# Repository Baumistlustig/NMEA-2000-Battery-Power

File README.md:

# NMEA 2000 Battery Power

This is a project, which reads the voltage and current of a battery, and posts it to a NMEA 2000 BUS.

The project uses an ESP32 & the SN65HVD230 for CAN BUS communication. If the voltage falls under a certain value, a contactor will automatically disconnect the battery from the rest of the circuit to prevent drain. 

Additionally, it posts the voltage, current and temperature into the N2k bus where it can be worked with by other devices.

## Table of Contents

- [Electrical](/Electrical) A KiCad project 
- [Software](/Software) A PlatformIO project

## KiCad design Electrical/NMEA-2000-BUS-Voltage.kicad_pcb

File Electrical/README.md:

# Electrical

  The KiCad project

  ## Table of Contents

  - [Symbol](/Electrical/Symbol) The Symbols for the schematics
  - [Datasheets](/Electrical/Datasheets) Datasheets of the components
  - [3D-Models](/Electrical/3D-Models) 3D-Models for the PCB
  - [Footprints](/Electrical/Footprints) Footprins for the PCB

## Components-List

A list of all the electrical components I used for the project:

- [ESP32 WROOM-32E](/Electrical/Datasheets/esp32-wroom-32e.pdf) Microcontroller
- [SN65HVD230](/Electrical/Datasheets/sn76hvd230.pdf) CAN Transceiver
- [BME280](/Electrical/Datasheets/bme280.pdf) Environment temp- & humidity sensor
- [ADS131M08](/Electrical/Datasheets/ads131m08-q1.pdf) 24-bit, 8 channel ADC
- [HO 150-S-SP30.pdf](/Electrical/Datasheets/HO-150-S-SP30.pdf) 150A current transducer
- [IRFZ44N](/Electrical/Datasheets/IRFZ44N.pdf) N-Channel MOSFET
- [LM7850](/Electrical/Datasheets/MC7800-D.PDF) 12-5V voltage regulator
- [AMS1117](/Electrical/Datasheets/ams1117.pdf) 5-3.3V voltage regulator
- [B57703M](/Electrical/Datasheets/B57703M-Thermistor.pdf) 10k NTC Thermistor
- ([ADR4533](/Electrical/Datasheets/ADR4533.pdf) 3.3V reference voltage source)

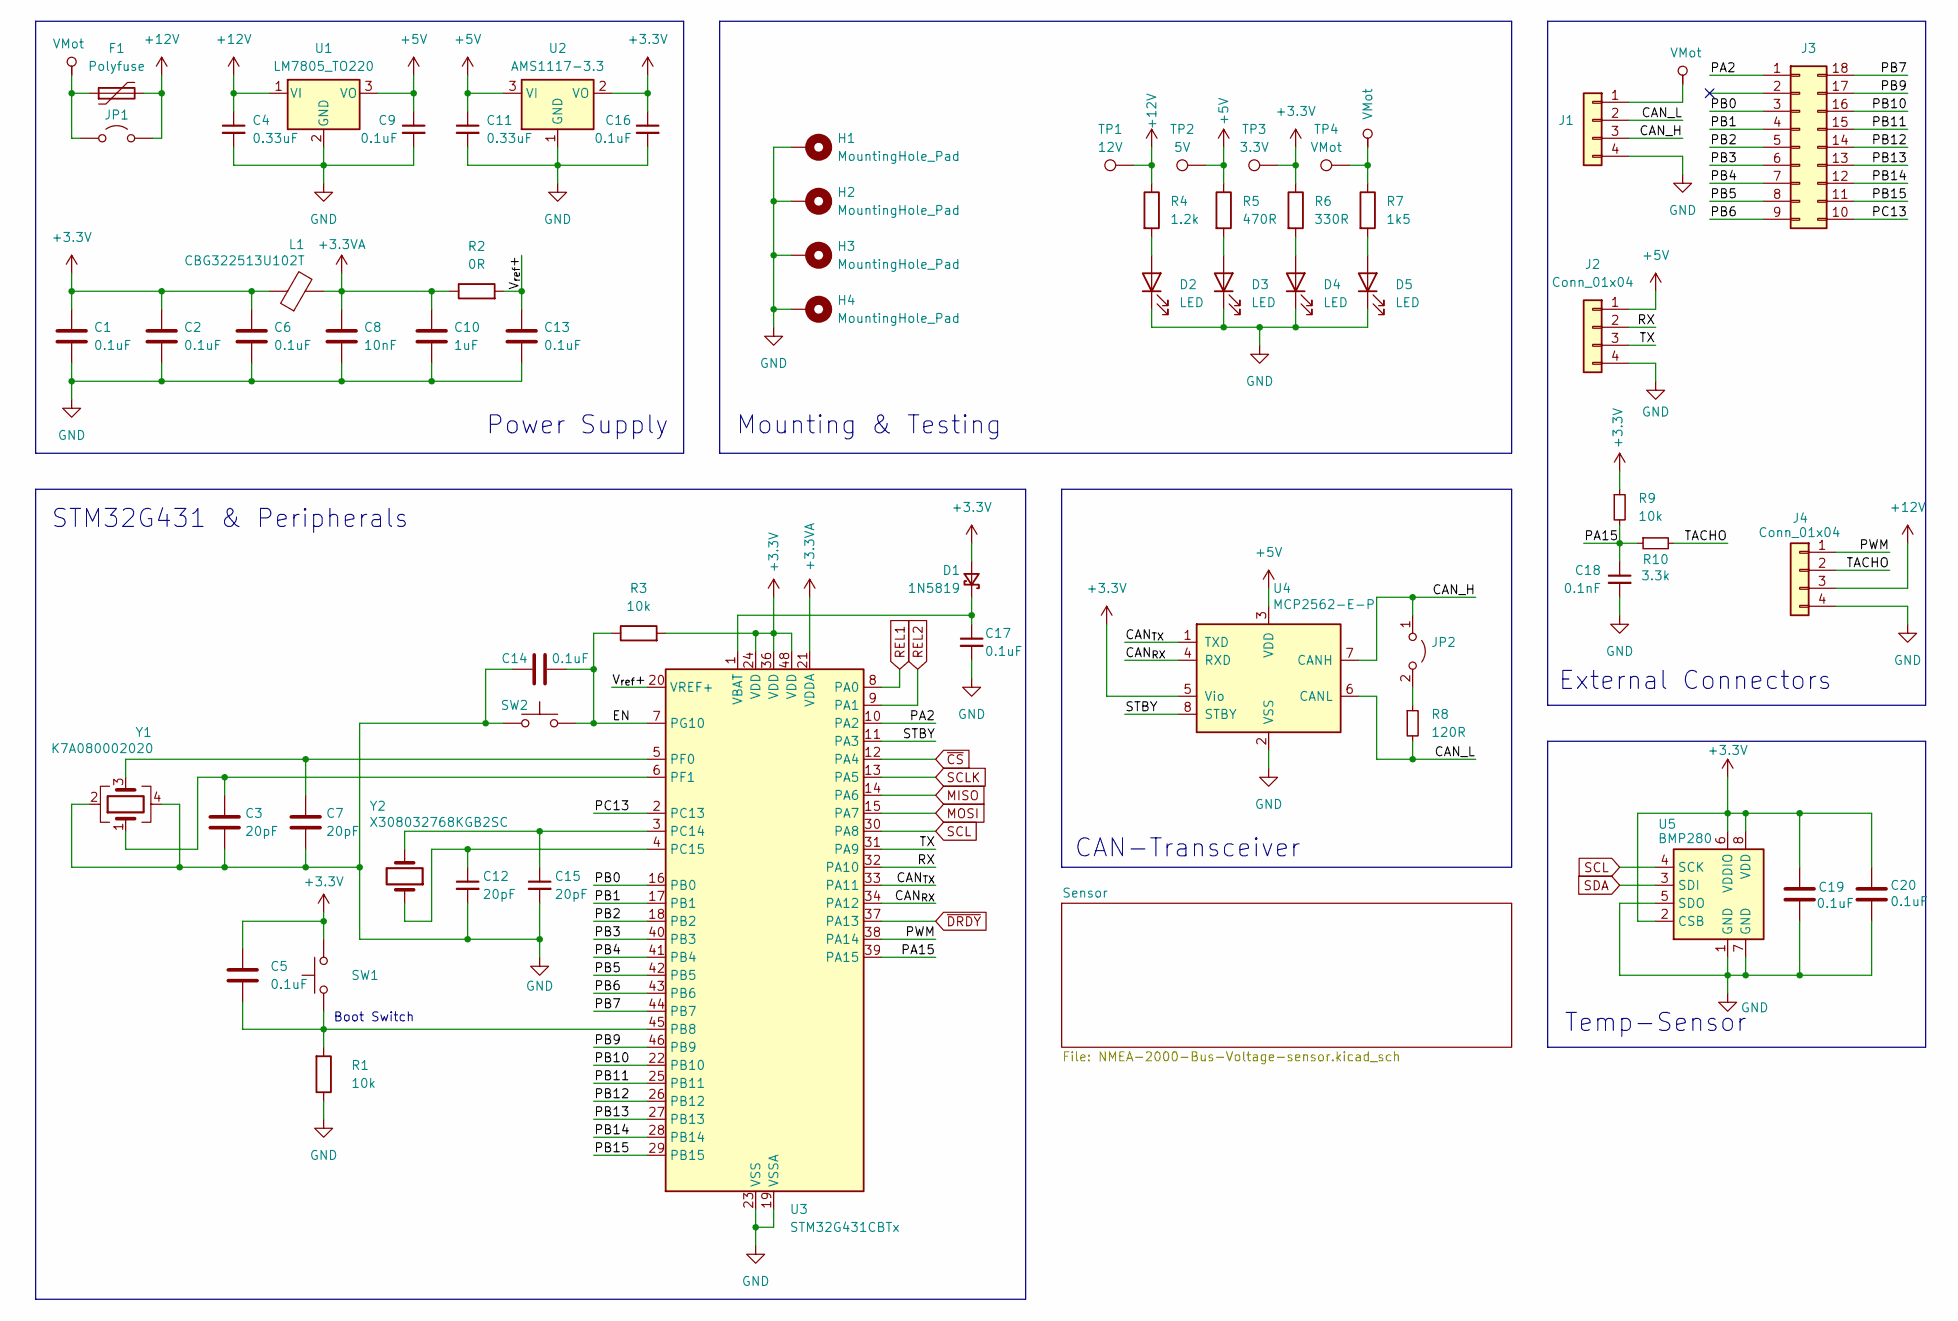
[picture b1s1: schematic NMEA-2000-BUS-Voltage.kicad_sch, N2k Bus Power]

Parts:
C1, C2, C5, C6, C9, C13, C14, C16, C17, C19, C20: 0.1uF; C_Disc_D5.0mm_W2.5mm_P5.00mm
C3, C7, C12, C15: 20pF; C_Disc_D5.0mm_W2.5mm_P5.00mm
C4, C11: 0.33uF; C_Disc_D5.0mm_W2.5mm_P5.00mm
C8: 10nF; C_Disc_D5.0mm_W2.5mm_P5.00mm
C10: 1uF; C_Disc_D5.0mm_W2.5mm_P5.00mm
C18: 0.1nF; C_Disc_D5.0mm_W2.5mm_P5.00mm
D1: 1N5819; D_DO-41_SOD81_P10.16mm_Horizontal
D2, D3, D4, D5: LED; LED_D5.0mm
F1: Polyfuse; D_1210_3225Metric_Pad1.42x2.65mm_HandSolder
H1, H2, H3, H4: MountingHole_Pad; MountingHole_6mm_Pad
J1: Conn_01x04; TerminalBlock_Phoenix_PT-1,5-4-5.0-H_1x04_P5.00mm_Horizontal
J2: Conn_01x04; PinSocket_1x04_P2.54mm_Horizontal
J3: Conn_02x08_Counter_Clockwise; PinHeader_2x09_P2.54mm_Vertical
J4: Conn_01x04; FanPinHeader_1x04_P2.54mm_Vertical
JP1, JP2: Jumper_2_Open; PinHeader_1x02_P2.54mm_Vertical
L1: CBG322513U102T; L_1210_3225Metric_Pad1.42x2.65mm_HandSolder
R1, R3, R9: 10k; R_Axial_DIN0207_L6.3mm_D2.5mm_P10.16mm_Horizontal
R2: 0R; R_Axial_DIN0207_L6.3mm_D2.5mm_P10.16mm_Horizontal
R4: 1.2k; R_Axial_DIN0207_L6.3mm_D2.5mm_P10.16mm_Horizontal
R5: 470R; R_Axial_DIN0207_L6.3mm_D2.5mm_P10.16mm_Horizontal
R6: 330R; R_Axial_DIN0207_L6.3mm_D2.5mm_P10.16mm_Horizontal
R7: 1k5; R_Axial_DIN0207_L6.3mm_D2.5mm_P10.16mm_Horizontal
R8: 120R; R_Axial_DIN0207_L6.3mm_D2.5mm_P10.16mm_Horizontal
R10: 3.3k; R_Axial_DIN0207_L6.3mm_D2.5mm_P10.16mm_Horizontal
SW1, SW2: SW_Push; SW_PUSH_6mm
TP1: 12V; TestPoint_Pad_3.0x3.0mm
TP2: 5V; TestPoint_Pad_3.0x3.0mm
TP3: 3.3V; TestPoint_Pad_3.0x3.0mm
TP4: VMot; TestPoint_Pad_3.0x3.0mm
U1: LM7805_TO220; TO-220-3_Vertical
U2: AMS1117-3.3; SOT-223-3_TabPin2
U3: STM32G431CBTx; LQFP-48_7x7mm_P0.5mm
U4: MCP2562-E-P; DIP-8_W7.62mm
U5: BMP280; Bosch_LGA-8_2x2.5mm_P0.65mm_ClockwisePinNumbering
Y1: K7A080002020; Crystal_SMD_7050-4Pin_7.0x5.0mm
Y2: X308032768KGB2SC; Crystal_C38-LF_D3.0mm_L8.0mm_Horizontal

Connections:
+3.3V: C1.1, C2.1, C5.1, C6.1, C16.1, C19.1, C20.1, D1.2 (A), L1.1, R3.2, R6.1, R9.1, SW1.1, TP3.1, U2.2 (VO), U3.24 (VDD), U3.36 (VDD), U3.48 (VDD), U4.5 (Vio), U5.2 (CSB), U5.6 (VDDIO), U5.8 (VDD); also elsewhere on the board
+3.3VA: C8.1, C10.1, L1.2, R2.1, U3.21 (VDDA)
+5V: C9.1, C11.1, J2.1, R5.1, TP2.1, U1.3 (VO), U2.3 (VI), U4.3 (VDD); also elsewhere on the board
+12V: C4.1, F1.2, J4.3, JP1.2 (B), R4.1, TP1.1, U1.1 (VI); also elsewhere on the board
/CAN_H: J1.3, JP2.1 (A), U4.7 (CANH)
/CAN_L: J1.2, R8.2, U4.6 (CANL)
/CAN_{RX}: U3.34 (PA12), U4.4 (RXD)
/CAN_{TX}: U3.33 (PA11), U4.1 (TXD)
/EN: C14.2, R3.1, SW2.2, U3.7 (PG10)
/PA2: J3.1, U3.10 (PA2)
/PA15: C18.1, R9.2, R10.1, U3.39 (PA15)
/PB0: J3.3, U3.16 (PB0)
/PB1: J3.4, U3.17 (PB1)
/PB2: J3.5, U3.18 (PB2)
/PB3: J3.6, U3.40 (PB3)
/PB4: J3.7, U3.41 (PB4)
/PB5: J3.8, U3.42 (PB5)
/PB6: J3.9, U3.43 (PB6)
/PB7: J3.18, U3.44 (PB7)
/PB9: J3.17, U3.46 (PB9)
/PB10: J3.16, U3.22 (PB10)
/PB11: J3.15, U3.25 (PB11)
/PB12: J3.14, U3.26 (PB12)
/PB13: J3.13, U3.27 (PB13)
/PB14: J3.12, U3.28 (PB14)
/PB15: J3.11, U3.29 (PB15)
/PC13: J3.10, U3.2 (PC13)
/PWM: J4.1, U3.38 (PA14)
/RX: J2.2, U3.32 (PA10)
/STBY: U3.11 (PA3), U4.8 (STBY)
/TACHO: J4.2, R10.2
/TX: J2.3, U3.31 (PA9)
/V_{ref}+: C13.1, R2.2, U3.20 (VREF+)
GND: C1.2, C2.2, C3.2, C4.2, C6.2, C7.2, C8.2, C9.2, C10.2, C11.2, C12.2, C13.2, C14.1, C15.2, C16.2, C17.2, C18.2, C19.2, C20.2, D2.1 (K), D3.1 (K), D4.1 (K), D5.1 (K), H1.1, H2.1, H3.1, H4.1, J1.4, J2.4, J4.4, R1.1, SW2.1, U1.2 (GND), U2.1 (GND), U3.19 (VSSA), U3.23 (VSS), U3.35 (VSS), U3.47 (VSS), U4.2 (VSS), U5.1 (GND), U5.5 (SDO), U5.7 (GND), Y1.2, Y1.4; also elsewhere on the board
MISO: U3.14 (PA6); also elsewhere on the board
MOSI: U3.15 (PA7); also elsewhere on the board
unnamed: C17.1, D1.1 (K), U3.1 (VBAT)
unnamed: D2.2 (A), R4.2
unnamed: D3.2 (A), R5.2
unnamed: D4.2 (A), R6.2
unnamed: D5.2 (A), R7.2
unnamed: JP2.2 (B), R8.1
unnamed: C5.2, R1.2, SW1.2, U3.45 (PB8)
unnamed: C15.1, U3.3 (PC14), Y2.2
unnamed: C12.1, U3.4 (PC15), Y2.1
unnamed: C7.1, U3.5 (PF0), Y1.3
unnamed: C3.1, U3.6 (PF1), Y1.1
REL1: U3.8 (PA0); also elsewhere on the board
REL2: U3.9 (PA1); also elsewhere on the board
SCL: U3.30 (PA8), U5.4 (SCK)
SCLK: U3.13 (PA5); also elsewhere on the board
SDA: U5.3 (SDI)
VMot: F1.1, J1.1, JP1.1 (A), R7.1, TP4.1
~CS: U3.12 (PA4); also elsewhere on the board
~DRDY: U3.37 (PA13); also elsewhere on the board

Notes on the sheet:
Power Supply
Mounting & Testing
STM32G431 & Peripherals
Boot Switch
External Connectors
CAN-Transceiver
Temp-Sensor

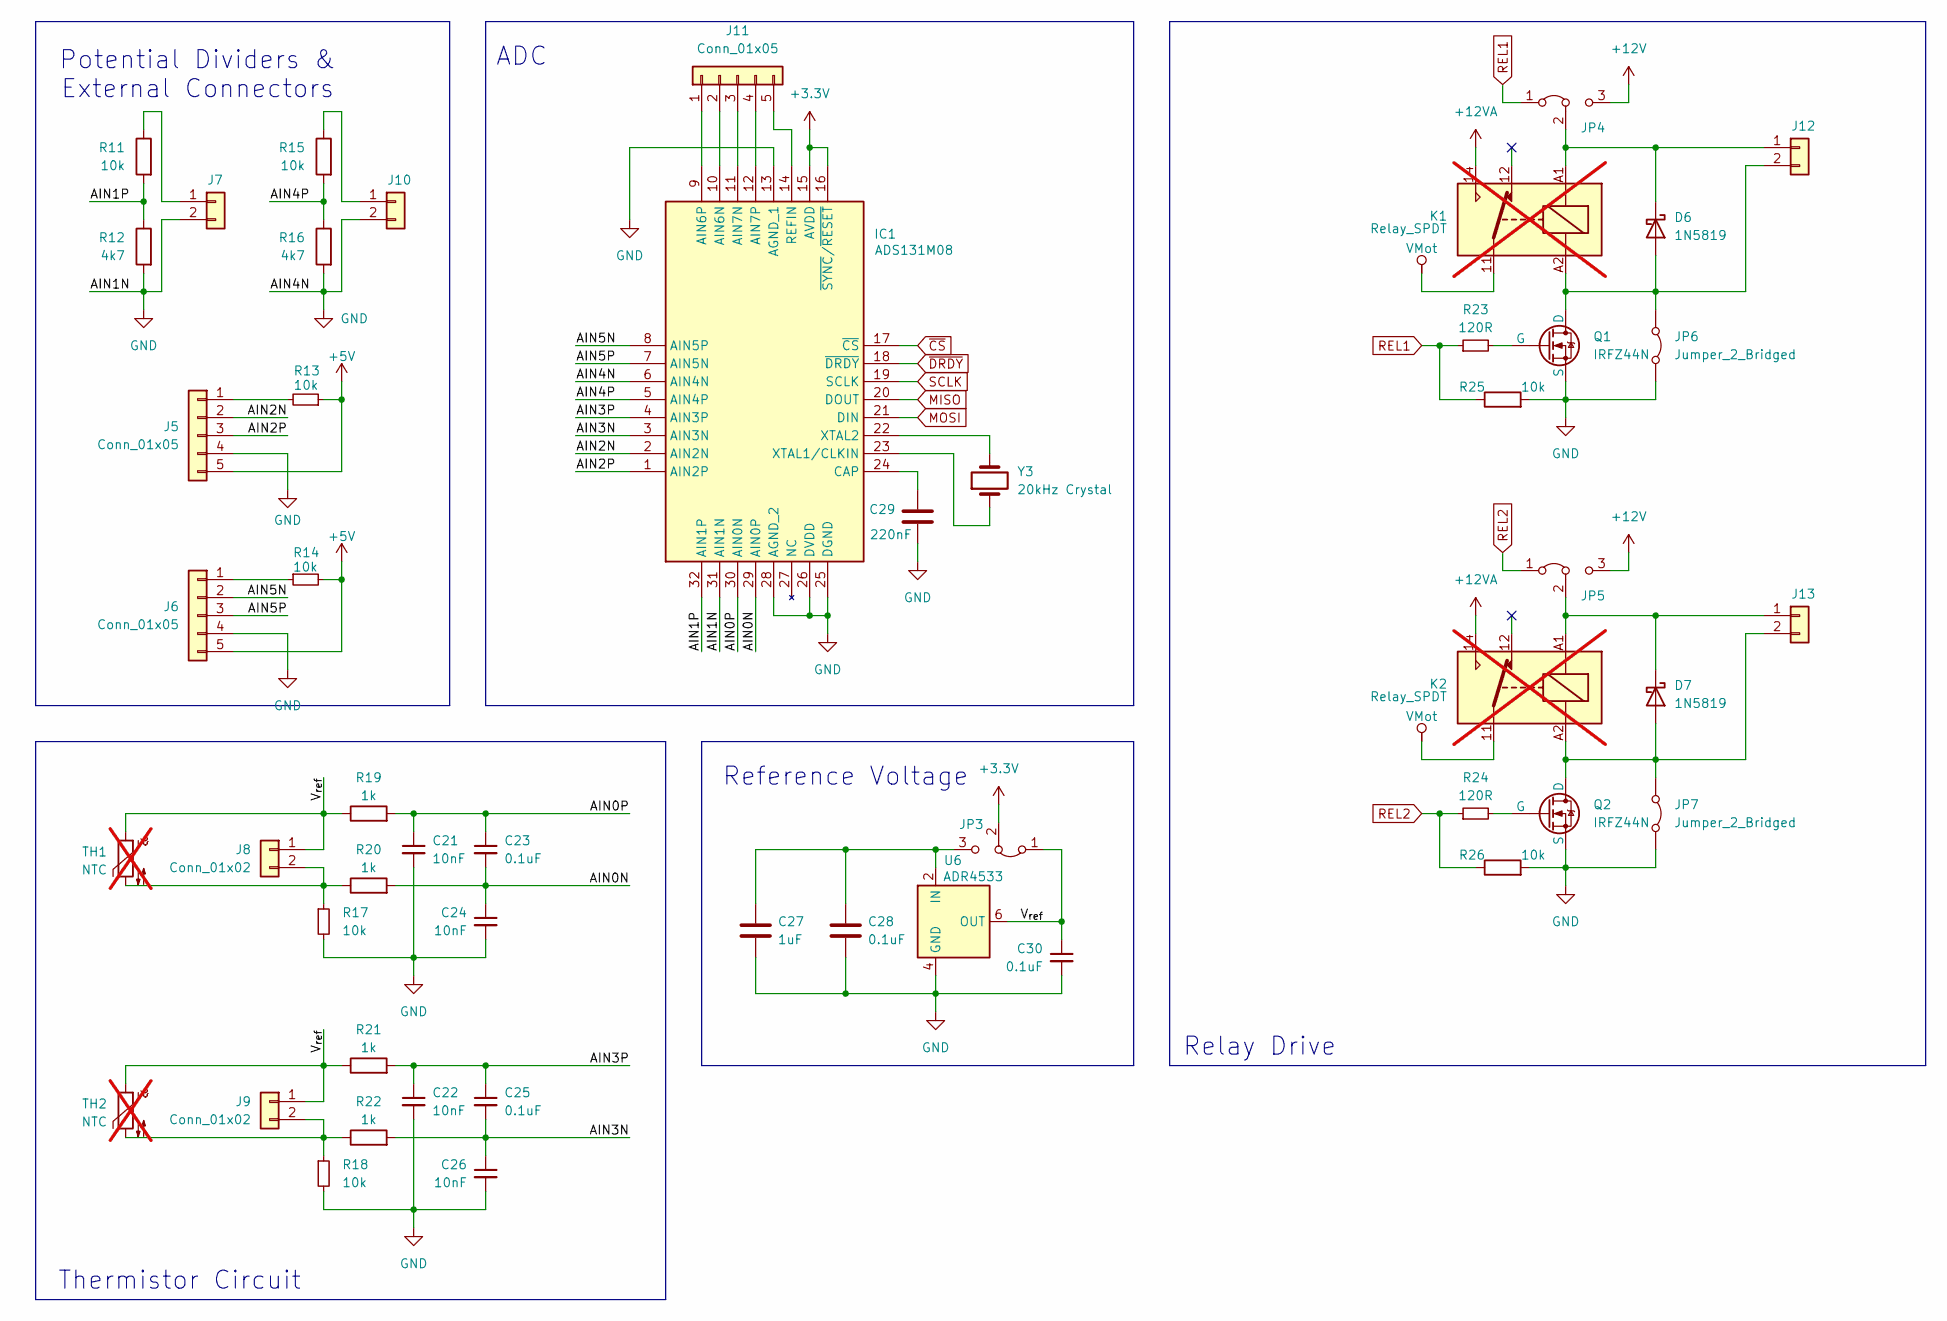
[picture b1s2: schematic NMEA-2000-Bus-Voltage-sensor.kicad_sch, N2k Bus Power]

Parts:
C21, C22, C24, C26: 10nF; C_Disc_D5.0mm_W2.5mm_P5.00mm
C23, C25, C28, C30: 0.1uF; C_Disc_D5.0mm_W2.5mm_P5.00mm
C27: 1uF; C_Disc_D5.0mm_W2.5mm_P5.00mm
C29: 220nF; C_Disc_D5.0mm_W2.5mm_P5.00mm
D6, D7: 1N5819; D_DO-41_SOD81_P10.16mm_Horizontal
IC1: ADS131M08; QFP50P700X700X120-32N; Mouser Part Number 595-ADS131M08QPBSRQ1
J5, J6: Conn_01x05; TerminalBlock_Phoenix_PT-1,5-5-5.0-H_1x05_P5.00mm_Horizontal
J7, J8, J9, J10, J12, J13: Conn_01x02; TerminalBlock_Phoenix_PT-1,5-2-5.0-H_1x02_P5.00mm_Horizontal
J11: Conn_01x05; PinHeader_1x05_P2.54mm_Vertical
JP3, JP4, JP5: Jumper_3_Bridged12; PinHeader_1x03_P2.54mm_Vertical
JP6, JP7: Jumper_2_Bridged; PinHeader_1x02_P2.54mm_Vertical
K1, K2: Relay_SPDT; not fitted
Q1, Q2: IRFZ44N; TO-220-3_Vertical
R11, R13, R14, R15, R17, R18, R25, R26: 10k; R_Axial_DIN0207_L6.3mm_D2.5mm_P10.16mm_Horizontal
R12, R16: 4k7; R_Axial_DIN0207_L6.3mm_D2.5mm_P10.16mm_Horizontal
R19, R20, R21, R22: 1k; R_Axial_DIN0207_L6.3mm_D2.5mm_P10.16mm_Horizontal
R23, R24: 120R; R_Axial_DIN0207_L6.3mm_D2.5mm_P10.16mm_Horizontal
TH1, TH2: NTC; not fitted
U6: ADR4533; SOIC-8_3.9x4.9mm_P1.27mm
Y3: 20kHz Crystal; Crystal_AT310_D3.0mm_L10.0mm_Horizontal

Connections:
+3.3V: IC1.15 (AVDD), IC1.16 (~SYNC/~RESET), JP3.2 (C); also elsewhere on the board
+5V: J5.5, J6.5, R13.1, R14.2; also elsewhere on the board
+12V: JP4.3 (B), JP5.3 (B); also elsewhere on the board
/Sensor/AIN0N: C23.2, C24.1, IC1.29 (AIN0P), R20.2
/Sensor/AIN0P: C21.1, C23.1, IC1.30 (AIN0N), R19.2
/Sensor/AIN1P: IC1.32 (AIN1P), R11.2, R12.1
/Sensor/AIN2N: IC1.2 (AIN2N), J5.2
/Sensor/AIN2P: IC1.1 (AIN2P), J5.3
/Sensor/AIN3N: C25.2, C26.1, IC1.3 (AIN3N), R22.2
/Sensor/AIN3P: C22.1, C25.1, IC1.4 (AIN3P), R21.2
/Sensor/AIN4P: IC1.5 (AIN4P), R15.2, R16.1
/Sensor/AIN5N: IC1.8 (AIN5P), J6.2
/Sensor/AIN5P: IC1.7 (AIN5N), J6.3
/Sensor/V_{ref}: C30.1, J8.1, J9.1, JP3.1 (A), R19.1, R21.1, TH1.1, TH2.1, U6.6 (OUT)
GND: C21.2, C22.2, C24.2, C26.2, C27.2, C28.2, C29.2, C30.2, IC1.6 (AIN4N), IC1.13 (AGND_1), IC1.25 (DGND), IC1.26 (DVDD), IC1.28 (AGND_2), IC1.31 (AIN1N), J5.4, J6.4, J7.2, J10.2, JP6.2 (B), JP7.2 (B), Q1.3 (S), Q2.3 (S), R12.2, R16.2, R17.2, R18.2, R25.2, R26.2, U6.4 (GND); also elsewhere on the board
MISO: IC1.20 (DOUT); also elsewhere on the board
MOSI: IC1.21 (DIN); also elsewhere on the board
unnamed: D6.2 (A), J12.2, JP6.1 (A), K1.A2, Q1.1 (D)
unnamed: D6.1 (K), J12.1, JP4.2 (C), K1.A1
unnamed: D7.2 (A), J13.2, JP7.1 (A), K2.A2, Q2.1 (D)
unnamed: D7.1 (K), J13.1, JP5.2 (C), K2.A1
unnamed: IC1.10 (AIN6N), J11.2
unnamed: IC1.9 (AIN6P), J11.1
unnamed: IC1.11 (AIN7N), J11.3
unnamed: IC1.12 (AIN7P), J11.4
unnamed: C29.1, IC1.24 (CAP)
unnamed: IC1.14 (REFIN), J11.5
unnamed: IC1.23 (XTAL1/CLKIN), Y3.1
unnamed: IC1.22 (XTAL2), Y3.2
unnamed: J5.1, R13.2
unnamed: J6.1, R14.1
unnamed: J7.1, R11.1
unnamed: J8.2, R17.1, R20.1, TH1.2
unnamed: J9.2, R18.1, R22.1, TH2.2
unnamed: J10.1, R15.1
unnamed: C27.1, C28.1, JP3.3 (B), U6.2 (IN)
unnamed: K1.11, K2.11
unnamed: K1.14, K2.14
unnamed: Q1.2 (G), R23.2
unnamed: Q2.2 (G), R24.2
REL1: JP4.1 (A), R23.1, R25.1; also elsewhere on the board
REL2: JP5.1 (A), R24.1, R26.1; also elsewhere on the board
SCLK: IC1.19 (SCLK); also elsewhere on the board
~CS: IC1.17 (~CS); also elsewhere on the board
~DRDY: IC1.18 (~DRDY); also elsewhere on the board

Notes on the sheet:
Potential Dividers & External Connectors
Reference Voltage
Relay Drive
Thermistor Circuit
ADC

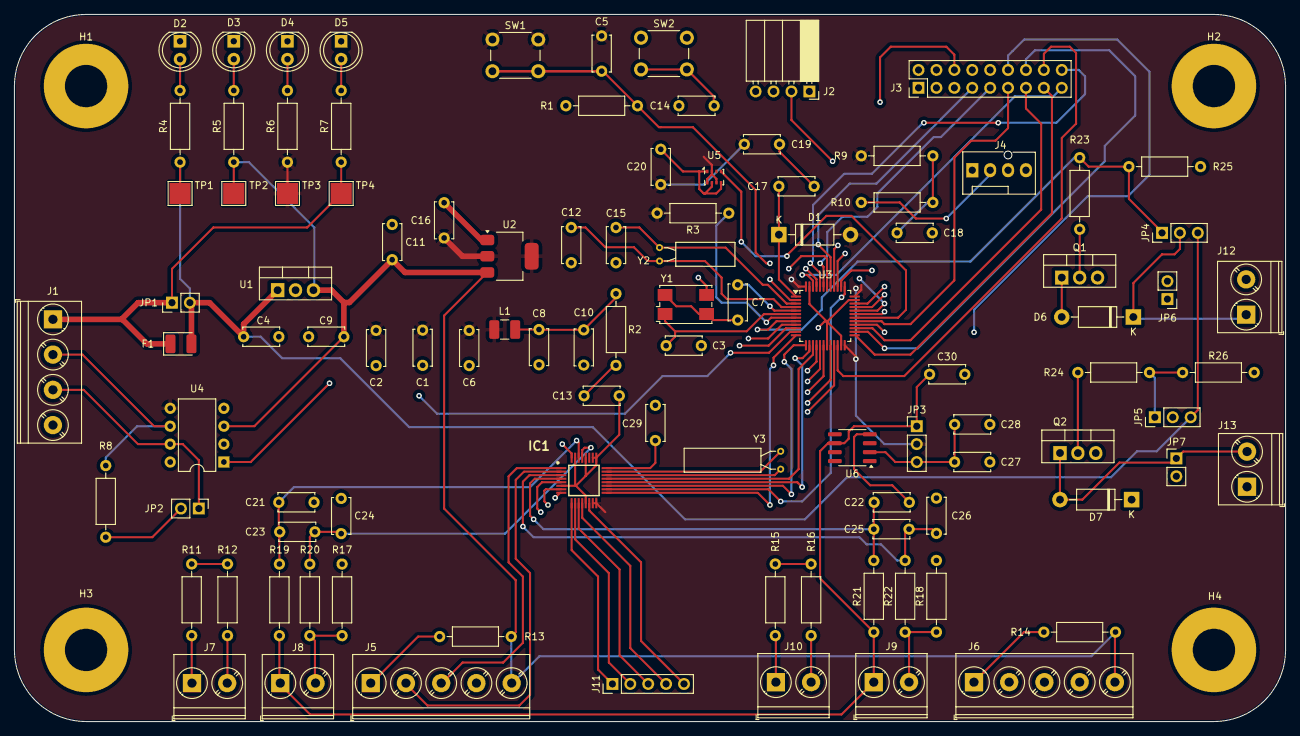
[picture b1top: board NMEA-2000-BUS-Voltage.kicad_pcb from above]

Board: 4 copper layers, 180.3 x 100.3 mm, 107 parts (0 on the bottom side), 86 nets.

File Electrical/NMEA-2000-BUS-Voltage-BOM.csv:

"Reference","Value","Datasheet","Footprint","Qty","DNP"
"C1,C2,C5,C6,C9,C13,C14,C16,C17,C19,C20,C23,C25,C28,C30","0.1uF","~","Capacitor_THT:C_Disc_D5.0mm_W2.5mm_P5.00mm","15",""
"C3,C7,C12,C15","20pF","~","Capacitor_THT:C_Disc_D5.0mm_W2.5mm_P5.00mm","4",""
"C4,C11","0.33uF","~","Capacitor_THT:C_Disc_D5.0mm_W2.5mm_P5.00mm","2",""
"C8,C21,C22,C24,C26","10nF","~","Capacitor_THT:C_Disc_D5.0mm_W2.5mm_P5.00mm","5",""
"C10,C27","1uF","~","Capacitor_THT:C_Disc_D5.0mm_W2.5mm_P5.00mm","2",""
"C18","0.1nF","~","Capacitor_THT:C_Disc_D5.0mm_W2.5mm_P5.00mm","1",""
"C29","220nF","~","Capacitor_THT:C_Disc_D5.0mm_W2.5mm_P5.00mm","1",""
"D1,D6,D7","1N5819","~","Diode_THT:D_DO-41_SOD81_P10.16mm_Horizontal","3",""
"D2,D3,D4,D5","LED","~","LED_THT:LED_D5.0mm","4",""
"F1","Polyfuse","~","Diode_SMD:D_1210_3225Metric_Pad1.42x2.65mm_HandSolder","1",""
"IC1","ADS131M08","https://www.ti.com/lit/ds/symlink/ads131m08-q1.pdf?HQS=dis-m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","ADS131M08QPBSRQ1:QFP50P700X700X120-32N","1",""
"J1,J2,J4","Conn_01x04","~","-- mixed values --","3",""
"J3","Conn_02x08_Counter_Clockwise","~","Connector_PinHeader_2.54mm:PinHeader_2x09_P2.54mm_Vertical","1",""
"J5,J6,J11","Conn_01x05","~","-- mixed values --","3",""
"J7,J8,J9,J10,J12,J13","Conn_01x02","~","TerminalBlock_Phoenix:TerminalBlock_Phoenix_PT-1,5-2-5.0-H_1x02_P5.00mm_Horizontal","6",""
"JP1,JP2","Jumper_2_Open","~","Connector_PinHeader_2.54mm:PinHeader_1x02_P2.54mm_Vertical","2",""
"JP6,JP7","Jumper_2_Bridged","~","Connector_PinHeader_2.54mm:PinHeader_1x02_P2.54mm_Vertical","2",""
"L1","CBG322513U102T","~","Inductor_SMD:L_1210_3225Metric_Pad1.42x2.65mm_HandSolder","1",""
"Q1,Q2","IRFZ44N","https://www.infineon.com/dgdl/Infineon-IRFZ44N-DataSheet-v01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","Package_TO_SOT_THT:TO-220-3_Vertical","2",""
"R1,R3,R9,R11,R13,R14,R15,R17,R18,R25,R26","10k","~","Resistor_THT:R_Axial_DIN0207_L6.3mm_D2.5mm_P10.16mm_Horizontal","11",""
"R2","0R","~","Resistor_THT:R_Axial_DIN0207_L6.3mm_D2.5mm_P10.16mm_Horizontal","1",""
"R4","1.2k","~","Resistor_THT:R_Axial_DIN0207_L6.3mm_D2.5mm_P10.16mm_Horizontal","1",""
"R5","470R","~","Resistor_THT:R_Axial_DIN0207_L6.3mm_D2.5mm_P10.16mm_Horizontal","1",""
"R6","330R","~","Resistor_THT:R_Axial_DIN0207_L6.3mm_D2.5mm_P10.16mm_Horizontal","1",""
"R7","1k5","~","Resistor_THT:R_Axial_DIN0207_L6.3mm_D2.5mm_P10.16mm_Horizontal","1",""
"R8,R23,R24","120R","~","Resistor_THT:R_Axial_DIN0207_L6.3mm_D2.5mm_P10.16mm_Horizontal","3",""
"R10","3.3k","~","Resistor_THT:R_Axial_DIN0207_L6.3mm_D2.5mm_P10.16mm_Horizontal","1",""
"R12,R16","4k7","~","Resistor_THT:R_Axial_DIN0207_L6.3mm_D2.5mm_P10.16mm_Horizontal","2",""
"R19,R20,R21,R22","1k","~","Resistor_THT:R_Axial_DIN0207_L6.3mm_D2.5mm_P10.16mm_Horizontal","4",""
"SW1,SW2","SW_Push","~","Button_Switch_THT:SW_PUSH_6mm","2",""
"TP1","12V","~","TestPoint:TestPoint_Pad_3.0x3.0mm","1",""
"TP2","5V","~","TestPoint:TestPoint_Pad_3.0x3.0mm","1",""
"TP3","3.3V","~","TestPoint:TestPoint_Pad_3.0x3.0mm","1",""
"TP4","VMot","~","TestPoint:TestPoint_Pad_3.0x3.0mm","1",""
"U1","LM7805_TO220","https://www.onsemi.cn/PowerSolutions/document/MC7800-D.PDF","Package_TO_SOT_THT:TO-220-3_Vertical","1",""
"U2","AMS1117-3.3","http://www.advanced-monolithic.com/pdf/ds1117.pdf","Package_TO_SOT_SMD:SOT-223-3_TabPin2","1",""
"U3","STM32G431CBTx","https://www.st.com/resource/en/datasheet/stm32g431cb.pdf","Package_QFP:LQFP-48_7x7mm_P0.5mm","1",""
"U4","MCP2562-E-P","http://ww1.microchip.com/downloads/en/DeviceDoc/25167A.pdf","Package_DIP:DIP-8_W7.62mm","1",""
"U5","BMP280","https://ae-bst.resource.bosch.com/media/_tech/media/datashee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","N2K-influx:Bosch_LGA-8_2x2.5mm_P0.65mm_ClockwisePinNumbering","1",""
"U6","ADR4533","https://www.analog.com/media/en/technical-documentation/data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","Package_SO:SOIC-8_3.9x4.9mm_P1.27mm","1",""
"Y1","K7A080002020","~","Crystal:Crystal_SMD_7050-4Pin_7.0x5.0mm","1",""
"Y2","X308032768KGB2SC","~","Crystal:Crystal_C38-LF_D3.0mm_L8.0mm_Horizontal","1",""
"Y3","20kHz Crystal","~","Crystal:Crystal_AT310_D3.0mm_L10.0mm_Horizontal","1",""

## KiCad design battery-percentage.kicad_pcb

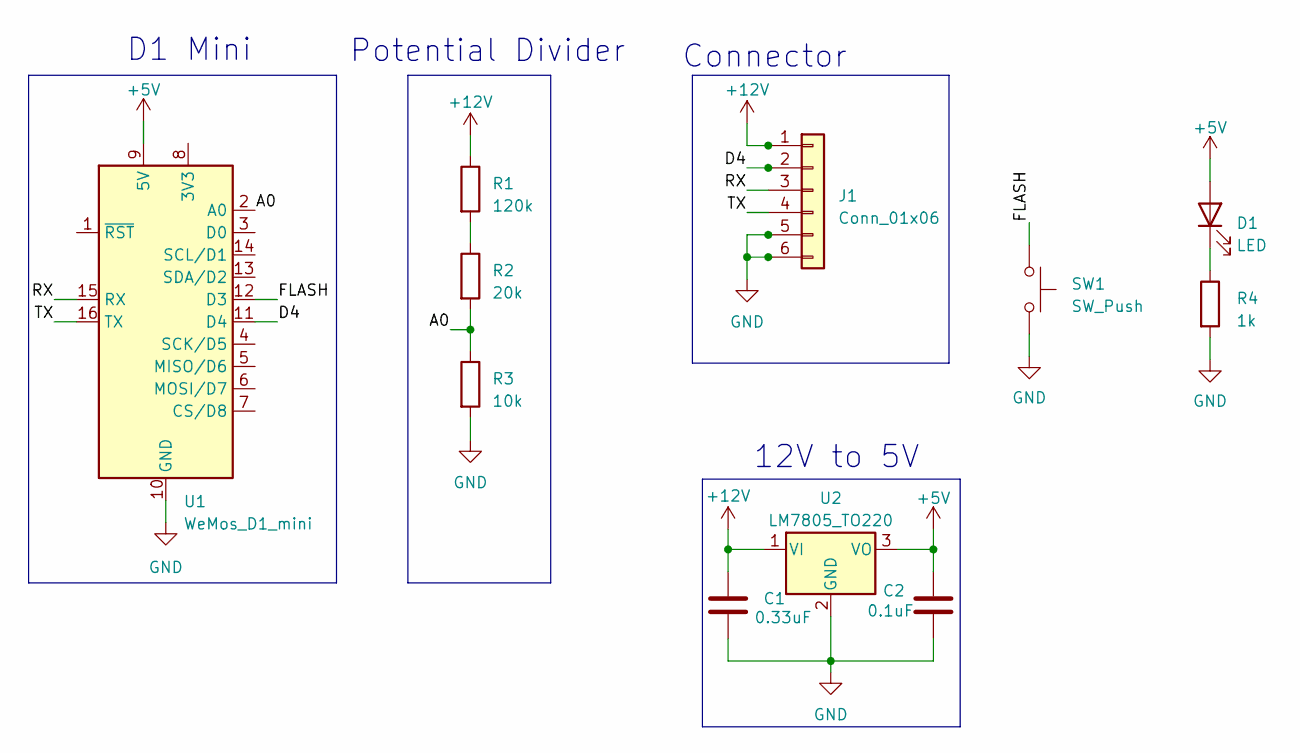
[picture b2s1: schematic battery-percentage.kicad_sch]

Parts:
C1: 0.33uF; CP_Radial_D4.0mm_P1.50mm
C2: 0.1uF; CP_Radial_D4.0mm_P1.50mm
D1: LED; LED_D1.8mm_W3.3mm_H2.4mm
J1: Conn_01x06; PinHeader_1x06_P2.00mm_Horizontal
R1: 120k; R_Axial_DIN0204_L3.6mm_D1.6mm_P5.08mm_Horizontal
R2: 20k; R_Axial_DIN0204_L3.6mm_D1.6mm_P5.08mm_Horizontal
R3: 10k; R_Axial_DIN0204_L3.6mm_D1.6mm_P5.08mm_Horizontal
R4: 1k; R_Axial_DIN0204_L3.6mm_D1.6mm_P5.08mm_Horizontal
SW1: SW_Push; SW_TH_Tactile_Omron_B3F-10xx
U1: WeMos_D1_mini; WEMOS_D1_mini_light
U2: LM7805_TO220; TO-220-3_Vertical

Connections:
+5V: C2.1, D1.2 (A), U1.9 (5V), U2.3 (VO)
+12V: C1.1, J1.1, R1.1, U2.1 (VI)
/A0: R2.2, R3.1, U1.2 (A0)
/D4: J1.2, U1.11 (D4)
/FLASH: SW1.1, U1.12 (D3)
/RX: J1.3, U1.15 (RX)
/TX: J1.4, U1.16 (TX)
GND: C1.2, C2.2, J1.5, J1.6, R3.2, R4.2, SW1.2, U1.10 (GND), U2.2 (GND)
unnamed: D1.1 (K), R4.1
unnamed: R1.2, R2.1

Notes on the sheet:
Potential Divider
12V to 5V
D1 Mini
Connector

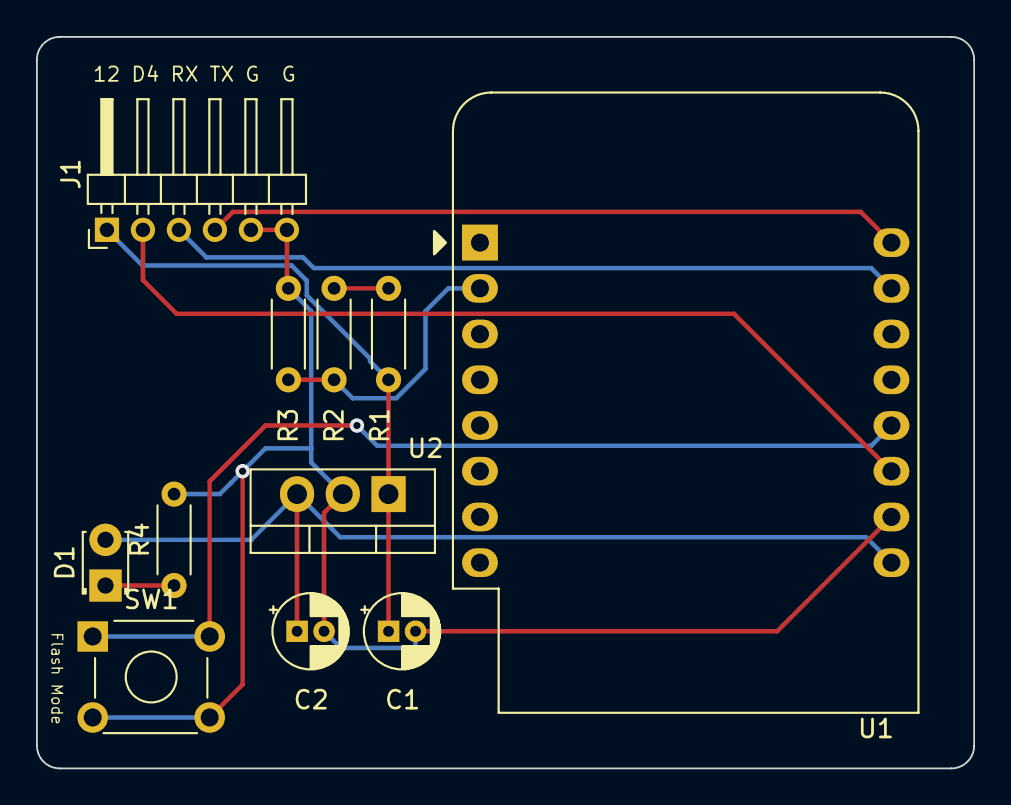
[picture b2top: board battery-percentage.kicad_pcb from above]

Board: 2 copper layers, 52.1 x 40.6 mm, 11 parts (0 on the bottom side), 10 nets.

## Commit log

2023-04-11 Initialized Kicad Project
2023-04-11 Added Schematic
2023-04-11 Added PCB Design
2023-04-11 Added Script
2023-04-11 Added TTl Interface to Schematic
2023-04-11 Added TTl Interface to PCB
2023-04-12 Added Express Server
2023-04-12 Added EJS
2023-04-13 Added POST / (Edit Voltage & State)
2023-04-13 Added posting voltage in script.ino
2023-04-13 Adjusted Ratio
2023-04-13 Updated Potential Divider
2023-04-20 Removed #auto_saved_files
2023-04-20 Updated Potential Divider & Capacitor
2023-04-27 Added Auto-Off Relay
2023-04-27 Updated PCB
2023-04-27 Updated Schematic
2023-04-27 Added PDF of Schematic
2023-04-27 Updated server.js
2023-05-02 Updated Potential Divider Values
2023-05-03 Updated PDF
2023-05-14 Added CAN BUS Connector Socket
2023-05-14 Renamed Files
2023-05-14 Added Relay Connector
2023-05-16 Added 3.3V to D1
2023-05-22 Changed D1 Mini to ESP32 Wroom
2023-07-08 Moved into 'Electrical Folder'
2023-07-08 Added Scheam
2023-07-08 Added D1 Mini to Schematic
2023-07-08 Added Potential Divider
2023-07-08 Added Flash Button
2023-07-08 Added LM7805
2023-07-08 Added Connector
2023-07-08 Added MCP2515 Module Symbol
2023-07-08 git status
2023-07-11 Added NMEA-2000-BUS-Voltage.ino
2023-07-17 Removed Arduino Project+
2023-07-17 Added PlatformIO Projkect
2023-07-17 Added N2k Info
2023-07-17 Added CheckSourceAddressChange()
2023-07-17 Added sendBatteryInfo()
2023-07-18 Cleaned Code and added readADC()
2023-07-18 Removed MCP2515
2023-07-18 Added BMP280 Symbol
2023-07-18 Added SN65HVD230-Module Symbol
2023-07-18 Added SN65HVD230 Module to Schematic
2023-07-18 Added BMP280-Module to Schematic
2023-07-18 Added ACS712-Module
2023-07-18 Added ACS712-Module to Schematic
2023-07-18 Modified ACS712 Module Symbol
2023-07-18 Modified Schematic
2023-07-18 Addedd Relay
2023-07-18 Added esp32 Footprint
2023-12-11 Added 12-15V voltageboost
2023-12-11 Changed .gitignore
2023-12-11 Updated Schematics
2024-03-10 Updated to KiCad Version 8
2024-03-10 Added PWM Fan control
2024-03-12 Added Power LEDs & 12V SDC
2024-05-19 Finished Rev 1
2024-05-24 Finished Rev 1 Schematics
2024-05-24 Finished Rev 2 Schematics
2024-05-24 Added 3D-Models
2024-05-29 Rename HO 150-S-SP30.pdf to HO-150-S-SP30.pdf
2024-05-29 Rename B57703M Thermistor.pdf to B57703M-Thermistor.pdf
2024-05-29 Added Schematic SVG
2024-07-05 Added BMP-280 3D-File Removed BME-280 3D-File Added Resetable Fuse 3D-File
2024-07-05 Added AMS1117 Datasheet Removed AP2112 Datasheet Added BMP-280 Datasheet Added STM32 Reference Manual Removed ADS131m08-Q1 Datasheet Added ADS131m08 Datasheet Removed ESP32 Datasheet Added STM32g431C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
2024-07-05 Added ADS131M08 Footprint
2024-07-06 Replaced SN65HVD230 with MCP2562
2024-07-06 Cleaned Up Project Updated BOM Updated Naming
